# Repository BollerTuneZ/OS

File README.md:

# OS
BollerTuneZ Operating System

http://www.bollertunez.de/

git test

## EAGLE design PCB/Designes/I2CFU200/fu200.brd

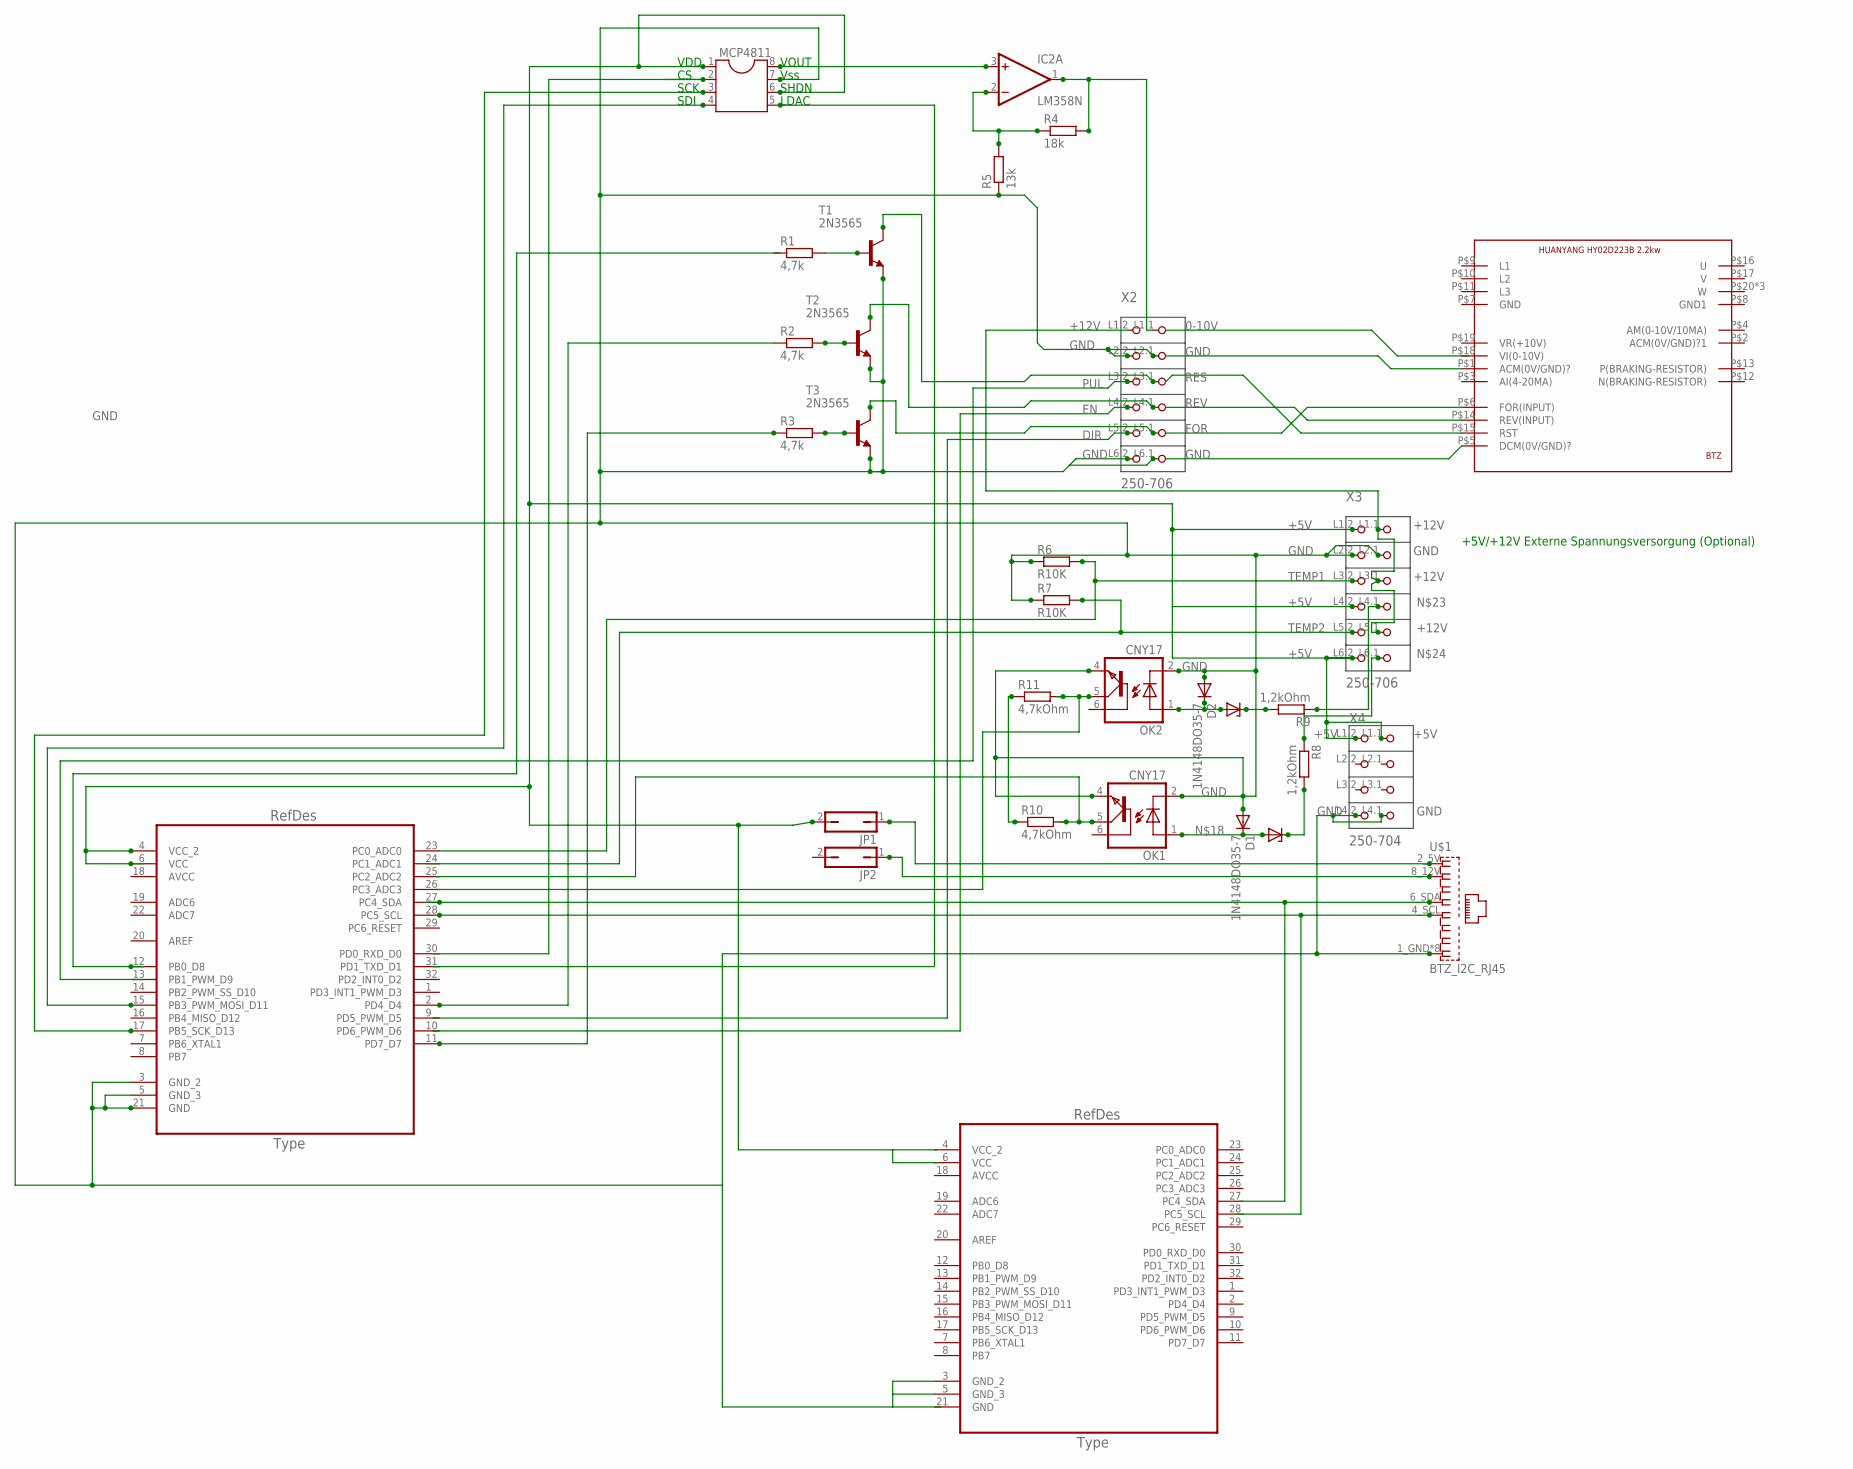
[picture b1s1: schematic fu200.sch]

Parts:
D1, D2: 1N4148DO35-7; DO35-7
IC2: LM358N; DIL08
JP1, JP2: JP1Q; JP1
MCP4811: DIL8; DIL08
OK1, OK2: CNY17; DIL06
R1, R2, R3: 4,7k; 0309/10
R4: 18k; 0204/7
R5: 13k; 0204/7
R6, R7: R10K; 0309/10
R8, R9: 1,2kOhm; 0204/7
R10, R11: 4,7kOhm; 0204/7
T1, T2, T3: 2N3565; TO92
U1, U2: ATMEGA328P-AU; QFP80P900X900X120-32N
U$1: BTZ_I2C_RJ45; RJ45
U$2: HUN_FU2
X2, X3: 250-706; P-250-706
X4: 250-704; P-250-704

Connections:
0-10V: IC2.1 (OUT), R4.2, X2.L1.1 (P1.1)
+5V: JP1.2, MCP4811.1, MCP4811.6, U1.4 (VCC_2), U1.6 (VCC), X3.L1.2 (P1.2), X3.L4.2 (P4.2), X3.L6.2 (P6.2), X4.L1.1 (P1.1), X4.L1.2 (P1.2)
+12V: X2.L1.2 (P1.2), X3.L1.1 (P1.1), X3.L3.1 (P3.1), X3.L5.1 (P5.1)
AVCC: U1.18 (AVCC), U2.18 (AVCC)
DIR: X2.L5.2 (P5.2)
EN: X2.L4.2 (P4.2)
FOR: T3.1 (C), X2.L5.1 (P5.1)
GND: D1.A, D2.A, MCP4811.7, OK1.2 (C), OK1.4 (EMI), OK2.2 (C), OK2.4 (EMI), R5.1, R6.1, R7.1, T1.3 (E), T2.3 (E), T3.3 (E), U1.3 (GND_2), U1.5 (GND_3), U1.21 (GND), U2.3 (GND_2), U2.5 (GND_3), U$1.1_GND (GND), U$1.3_GND (GND), U$1.5_GND (GND), U$1.7_GND (GND), U$1.G1 (GND), U$1.G2 (GND), U$1.G3 (GND), U$1.G4 (GND), X2.L2.1 (P2.1), X2.L2.2 (P2.2), X2.L6.1 (P6.1), X2.L6.2 (P6.2), X3.L2.1 (P2.1), X3.L2.2 (P2.2), X4.L4.1 (P4.1), X4.L4.2 (P4.2)
unnamed: R1.2, T1.2 (B)
unnamed: U1.27 (PC4_SDA), U$1.6_SDA (SDA)
unnamed: R3.2, T3.2 (B)
unnamed: U1.28 (PC5_SCL), U$1.4_SCL (SCL)
unnamed: JP2.1, U$1.8_12V (12V)
unnamed: JP1.1, U$1.2_5V (5V)
unnamed: R2.1, U1.2 (PD4_D4)
unnamed: R3.1, U1.11 (PD7_D7)
unnamed: R2.2, T2.2 (B)
unnamed: D1.C, OK1.1 (A)
unnamed: D2.C, OK2.1 (A)
unnamed: R10.1, R11.1
unnamed: OK2.5 (COL), R11.2
unnamed: R9.1, X3.L4.1 (P4.1)
unnamed: R8.1, X3.L6.1 (P6.1)
unnamed: OK1.5 (COL), R10.2
unnamed: IC2.3 (+IN), MCP4811.8
unnamed: MCP4811.3, U1.17 (PB5_SCK_D13)
unnamed: MCP4811.4, U1.15 (PB3_PWM_MOSI_D11)
unnamed: IC2.2 (-IN), R4.1, R5.2
PUL: X2.L3.2 (P3.2)
RES: T1.1 (C), X2.L3.1 (P3.1)
REV: T2.1 (C), X2.L4.1 (P4.1)
TEMP1: R6.2, U1.23 (PC0_ADC0), X3.L3.2 (P3.2)
TEMP2: R7.2, X3.L5.2 (P5.2)
V+: IC2.8 (V+)
V-: IC2.4 (V-)
VCC: U2.6 (VCC)
VCC_2: U2.4 (VCC_2)

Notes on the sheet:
VDD
SCK
SDI
VOUT
Vss
SHDN
LDAC
+5V/+12V Externe Spannungsversorgung (Optional)

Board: 2 copper layers, 29 parts (2 on the bottom side), 30 nets, no tracks yet.

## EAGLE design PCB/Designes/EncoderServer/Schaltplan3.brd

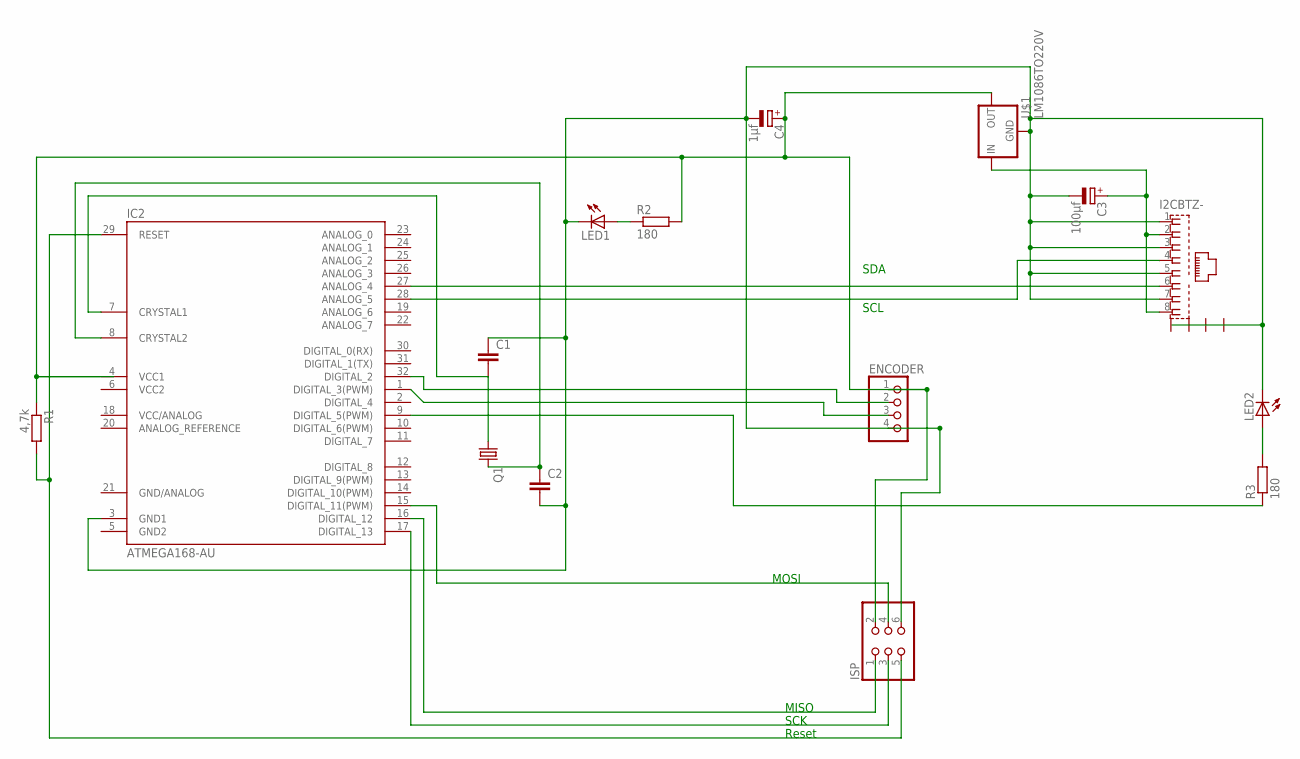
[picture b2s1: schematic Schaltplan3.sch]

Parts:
C1, C2: C-EU025-025X050; C025-025X050
C3: 100µf; E2,5-6
C4: 1µf; E2,5-6
ENCODER: PINHD-1X4; 1X04
I2CBTZ: RJ45
IC2: ATMEGA168-AU; TQFP32-08
ISP: PINHD-2X3; 2X03
LED1, LED2: LED5MM
Q1: CRYSTALHC49S; HC49/S
R1: 4,7k; 0204/7
R2, R3: 180; 0204/7
U$1: LM1086TO220V; TO220S

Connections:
GND2: IC2.5 (GND2)
GND/ANALOG: IC2.21 (GND/ANALOG)
unnamed: LED2.A, R3.2
unnamed: IC2.29 (RESET), ISP.5, R1.2
unnamed: C4.+, ENCODER.1, IC2.4 (VCC1), ISP.2, R1.1, R2.2, U$1.2 (OUT)
unnamed: C3.+, I2CBTZ.2, I2CBTZ.8, U$1.3 (IN)
unnamed: C1.2, IC2.7 (CRYSTAL1), Q1.1
unnamed: I2CBTZ.4, IC2.28 (ANALOG_5)
unnamed: I2CBTZ.6, IC2.27 (ANALOG_4)
unnamed: C2.1, IC2.8 (CRYSTAL2), Q1.2
unnamed: C1.1, C2.2, C3.-, C4.-, ENCODER.4, I2CBTZ.1, I2CBTZ.3, I2CBTZ.5, I2CBTZ.7, IC2.3 (GND1), ISP.6, LED1.K (C), LED2.K (C), U$1.1 (GND)
unnamed: ENCODER.3, IC2.1 (DIGITAL_3(PWM))
unnamed: ENCODER.2, IC2.32 (DIGITAL_2)
unnamed: IC2.17 (DIGITAL_13), ISP.3
unnamed: IC2.9 (DIGITAL_5(PWM)), R3.1
unnamed: LED1.A, R2.1
unnamed: IC2.16 (DIGITAL_12), ISP.1
unnamed: IC2.15 (DIGITAL_11(PWM)), ISP.4
VCC2: IC2.6 (VCC2)

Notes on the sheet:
MISO
SCK
MOSI
Reset
SDA
SCL

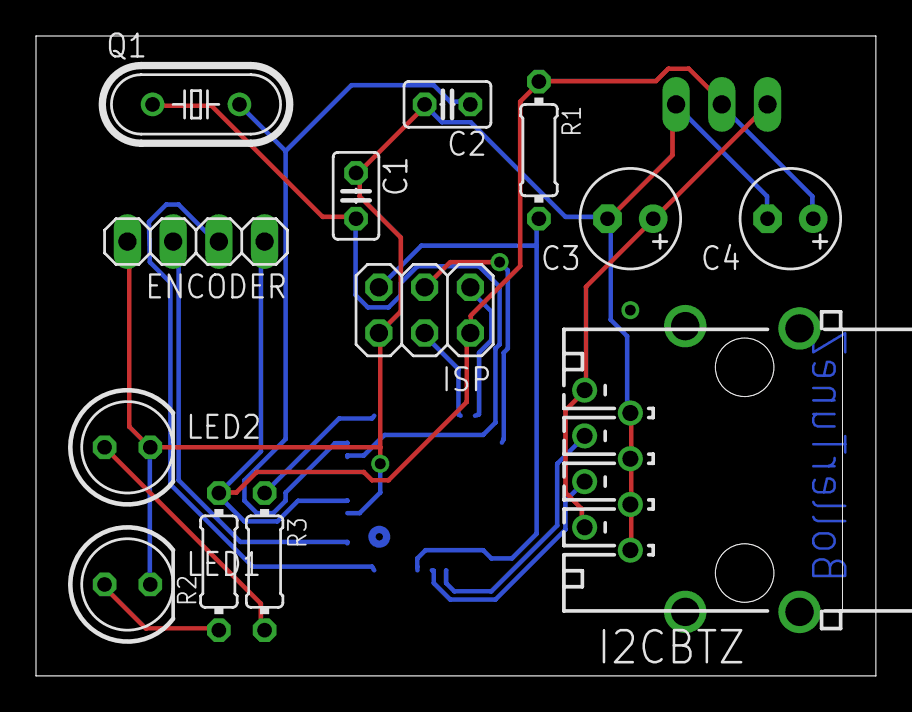
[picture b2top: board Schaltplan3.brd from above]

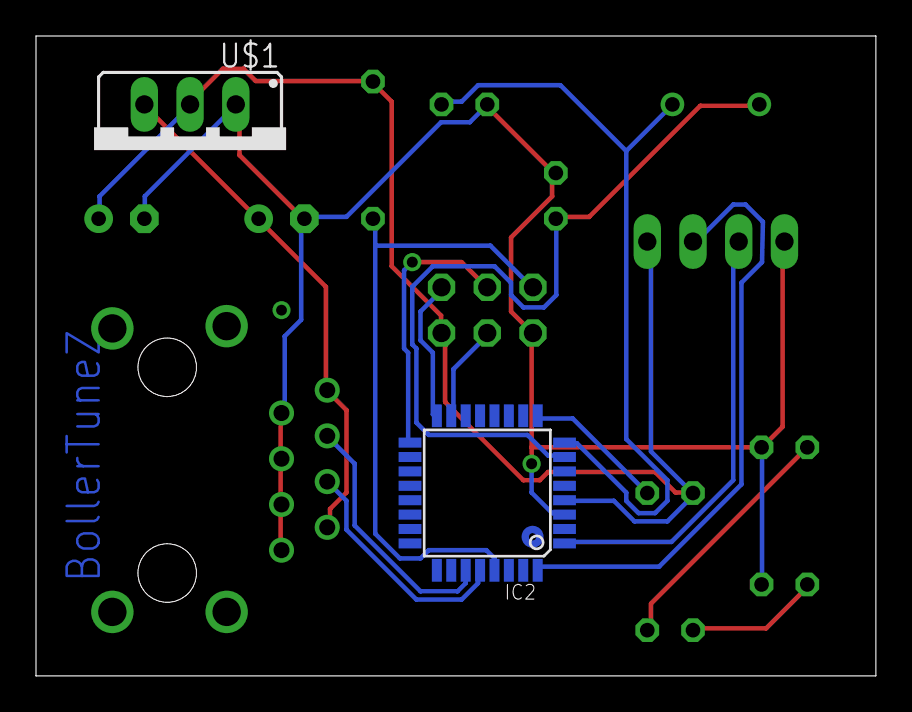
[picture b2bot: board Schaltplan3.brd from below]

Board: 2 copper layers, 46.7 x 35.6 mm, 15 parts (2 on the bottom side), 16 nets.

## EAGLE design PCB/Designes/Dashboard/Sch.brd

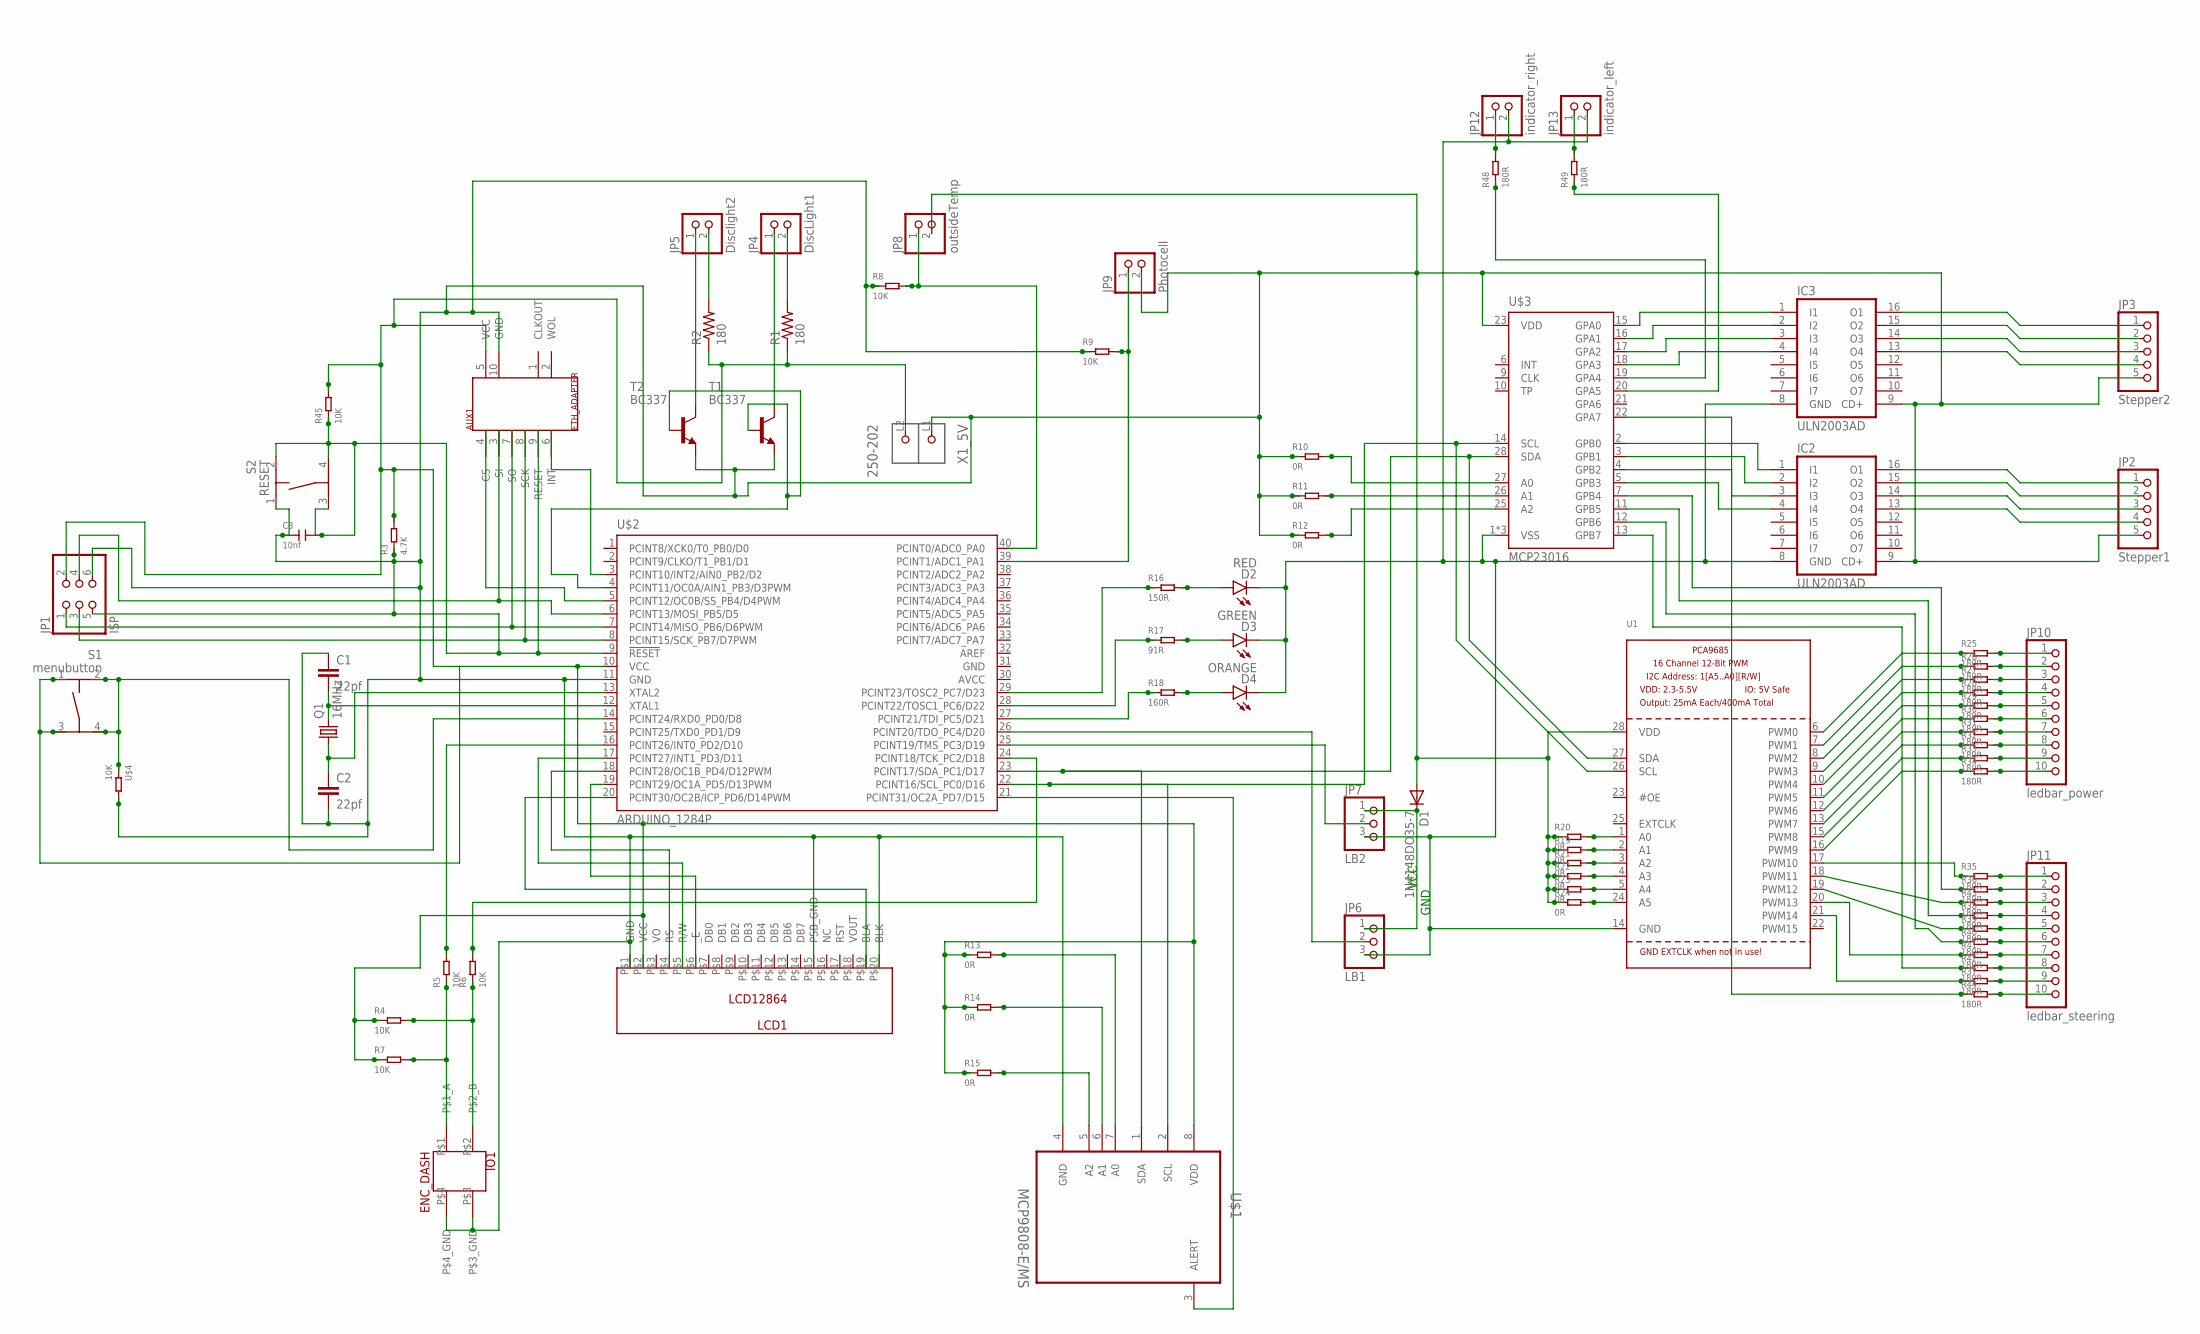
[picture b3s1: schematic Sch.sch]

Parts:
AUX1: ETH_ADAPTER; PINHEAD5X5
C1, C2: 22pf; C025-025X050
C3: 10nf; C0603
D1: 1N4148DO35-7; DO35-7
D2: RED; LED-0603
D3: GREEN; LED-0603
D4: ORANGE; LED-0603
IC2, IC3: ULN2003AD; SO16
IO1: ENC_DASH; PINHEAD2X2
JP1: ISP; 2X03
JP2: Stepper1; 1X05
JP3: Stepper2; 1X05
JP4: DiscLight1; 1X02
JP5: Disclight2; 1X02
JP6: LB1; 1X03
JP7: LB2; 1X03
JP8: outsideTemp; 1X02
JP9: Photocell; 1X02
JP10: ledbar_power; 1X10
JP11: ledbar_steering; 1X10
JP12: indicator_right; 1X02
JP13: indicator_left; 1X02
LCD1: LCD12864; PINHEAD1X20
Q1: 16MHz; HC49/S
R1, R2: 180; 0805-THM
R3: 4.7K; R0603
R4, R5, R6, R7, R8, R9, R45: 10K; R0603
R10, R11, R12, R13, R14, R15, R19, R20, R21, R22, R23, R24: 0R; R0603
R16: 150R; R0603
R17: 91R; R0603
R18: 160R; R0603
R25, R26, R27, R28, R29, R30, R31, R32, R33, R34, R35, R36, R37, R38, R39, R40, R41, R42, R43, R44, R48, R49: 180R; R0603
S1: menubutton; TASTER-9314_SMD
S2: RESET; TASTER-9314_SMD
T1, T2: BC337; TO92
U1: PCA9685; TSSOP28
U$1: MCP9808-E/MS; SOP65P490X110-8N
U$2: ARDUINO_1284P; DIL40
U$3: MCP23016; SO28W
U$4: 10K; R0805
X1_5V: 250-202; P-250-202

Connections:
AVCC: U$2.30 (AVCC)
DISCLIGHT1: T1.2 (B), T2.2 (B), U$2.4 (PCINT11/OC0A/AIN1_PB3/D3PWM)
GND: U$2.31 (GND)
unnamed: IC2.16 (O1), JP2.1
unnamed: IC2.15 (O2), JP2.2
unnamed: IC2.14 (O3), JP2.3
unnamed: IC2.13 (O4), JP2.4
unnamed: IC3.16 (O1), JP3.1
unnamed: IC3.15 (O2), JP3.2
unnamed: IC3.14 (O3), JP3.3
unnamed: IC3.13 (O4), JP3.4
unnamed: R36.1, U$3.7 (GPB4)
unnamed: JP5.1, T2.3 (C)
unnamed: JP5.2, R2.2
unnamed: JP4.2, R1.2
unnamed: JP4.1, T1.3 (C)
unnamed: S1.2, S1.4, U$2.14 (PCINT24/RXD0_PD0/D8), U$4.1
unnamed: IC3.1 (I1), U$3.15 (GPA0)
unnamed: C2.1, Q1.1, U$2.13 (XTAL2)
unnamed: IC3.2 (I2), U$3.16 (GPA1)
unnamed: C1.2, Q1.2, U$2.12 (XTAL1)
unnamed: IC3.3 (I3), U$3.17 (GPA2)
unnamed: D1.C, JP6.1, JP7.1
unnamed: R11.2, U$3.26 (A1)
unnamed: AUX1.7 (SO), JP1.1, U$2.7 (PCINT14/MISO_PB6/D6PWM)
unnamed: AUX1.8 (SCK), JP1.3, U$2.8 (PCINT15/SCK_PB7/D7PWM)
unnamed: IC3.4 (I4), U$3.18 (GPA3)
unnamed: AUX1.3 (SI), JP1.4, U$2.6 (PCINT13/MOSI_PB5/D5)
unnamed: R38.1, U$3.11 (GPB5)
unnamed: U$1.3 (ALERT), U$2.21 (PCINT31/OC2A_PD7/D15)
unnamed: IO1.P$2 (P$2_B), R4.2, R6.1
unnamed: AUX1.6 (INT), U$2.3 (PCINT10/INT2/AIN0_PB2/D2)
unnamed: AUX1.4 (CS), U$2.5 (PCINT12/OC0B/SS_PB4/D4PWM)
unnamed: U1.26 (SCL), U$1.2 (SCL), U$2.22 (PCINT16/SCL_PC0/D16), U$3.14 (SCL)
unnamed: U1.27 (SDA), U$1.1 (SDA), U$2.23 (PCINT17/SDA_PC1/D17), U$3.28 (SDA)
unnamed: IO1.P$1 (P$1_A), R5.1, R7.2
unnamed: IC2.1 (I1), U$3.2 (GPB0)
unnamed: IC2.2 (I2), U$3.3 (GPB1)
unnamed: LCD1.P$4 (RS), U$2.18 (PCINT28/OC1B_PD4/D12PWM)
unnamed: LCD1.P$5 (R/W), U$2.17 (PCINT27/INT1_PD3/D11)
unnamed: LCD1.P$6 (_E), U$2.19 (PCINT29/OC1A_PD5/D13PWM)
unnamed: LCD1.P$19 (BLA), U$2.20 (PCINT30/OC2B/ICP_PD6/D14PWM)
unnamed: R5.2, U$2.16 (PCINT26/INT0_PD2/D10)
unnamed: R6.2, U$2.24 (PCINT18/TCK_PC2/D18)
unnamed: IC2.3 (I3), U$3.4 (GPB2)
unnamed: IC2.4 (I4), U$3.5 (GPB3)
unnamed: R14.2, U$1.6 (A1)
unnamed: JP7.2, U$2.25 (PCINT19/TMS_PC3/D19)
unnamed: JP6.2, U$2.26 (PCINT20/TDO_PC4/D20)
unnamed: JP8.1, R8.2, U$2.40 (PCINT0/ADC0_PA0)
unnamed: R10.2, U$3.27 (A0)
unnamed: JP9.1, R9.2, U$2.39 (PCINT1/ADC1_PA1)
unnamed: R41.1, U1.20 (PWM13)
unnamed: R12.2, U$3.25 (A2)
unnamed: R13.2, U$1.7 (A0)
unnamed: R15.2, U$1.5 (A2)
unnamed: R39.1, U1.19 (PWM12)
unnamed: D2.A, R16.2
unnamed: D3.A, R17.2
unnamed: D4.A, R18.2
unnamed: R18.1, U$2.27 (PCINT21/TDI_PC5/D21)
unnamed: R17.1, U$2.28 (PCINT22/TOSC1_PC6/D22)
unnamed: R16.1, U$2.29 (PCINT23/TOSC2_PC7/D23)
unnamed: R24.2, U1.24 (A5)
unnamed: R23.2, U1.5 (A4)
unnamed: R22.2, U1.4 (A3)
unnamed: R21.2, U1.3 (A2)
unnamed: R19.2, U1.2 (A1)
unnamed: R20.2, U1.1 (A0)
unnamed: JP10.1, R25.2
unnamed: JP10.2, R26.2
unnamed: JP10.3, R27.2
unnamed: JP10.4, R28.2
unnamed: JP10.5, R29.2
unnamed: JP10.6, R30.2
unnamed: JP10.7, R31.2
unnamed: JP10.8, R32.2
unnamed: JP10.9, R33.2
unnamed: JP10.10, R34.2
unnamed: JP11.1, R35.2
unnamed: JP11.2, R36.2
unnamed: JP11.3, R43.2
unnamed: JP11.4, R38.2
unnamed: JP11.5, R39.2
unnamed: JP11.6, R40.2
unnamed: JP11.7, R41.2
unnamed: JP11.8, R42.2
unnamed: JP11.9, R37.2
unnamed: JP11.10, R44.2
unnamed: R25.1, U1.6 (PWM0)
unnamed: R26.1, U1.7 (PWM1)
unnamed: R27.1, U1.8 (PWM2)
unnamed: R28.1, U1.9 (PWM3)
unnamed: R29.1, U1.10 (PWM4)
unnamed: R30.1, U1.11 (PWM5)
unnamed: R31.1, U1.12 (PWM6)
unnamed: R32.1, U1.13 (PWM7)
unnamed: R33.1, U1.15 (PWM8)
unnamed: R34.1, U1.16 (PWM9)
unnamed: R35.1, U1.17 (PWM10)
unnamed: R43.1, U1.18 (PWM11)
unnamed: R37.1, U1.21 (PWM14)
unnamed: R40.1, U$3.12 (GPB6)
unnamed: AUX1.9 (RESET), C3.2, JP1.5, R45.1, S2.2, S2.3, S2.4, U$2.9 (!RESET)
unnamed: R42.1, U$3.13 (GPB7)
unnamed: R44.1, U$3.22 (GPA7)
unnamed: R48.1, U$3.19 (GPA4)
unnamed: R49.1, U$3.20 (GPA5)
unnamed: JP12.1, R48.2
unnamed: JP13.1, R49.2
unnamed: D2.C, D3.C, D4.C, IC2.8 (GND), IC3.8 (GND), JP6.3, JP7.3, JP12.2, JP13.2, U1.14 (GND), U$3.1 (VSS), U$3.8 (VSS), U$3.24 (VSS)
VCC: AUX1.5 (VCC)

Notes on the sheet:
VCC
GND

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
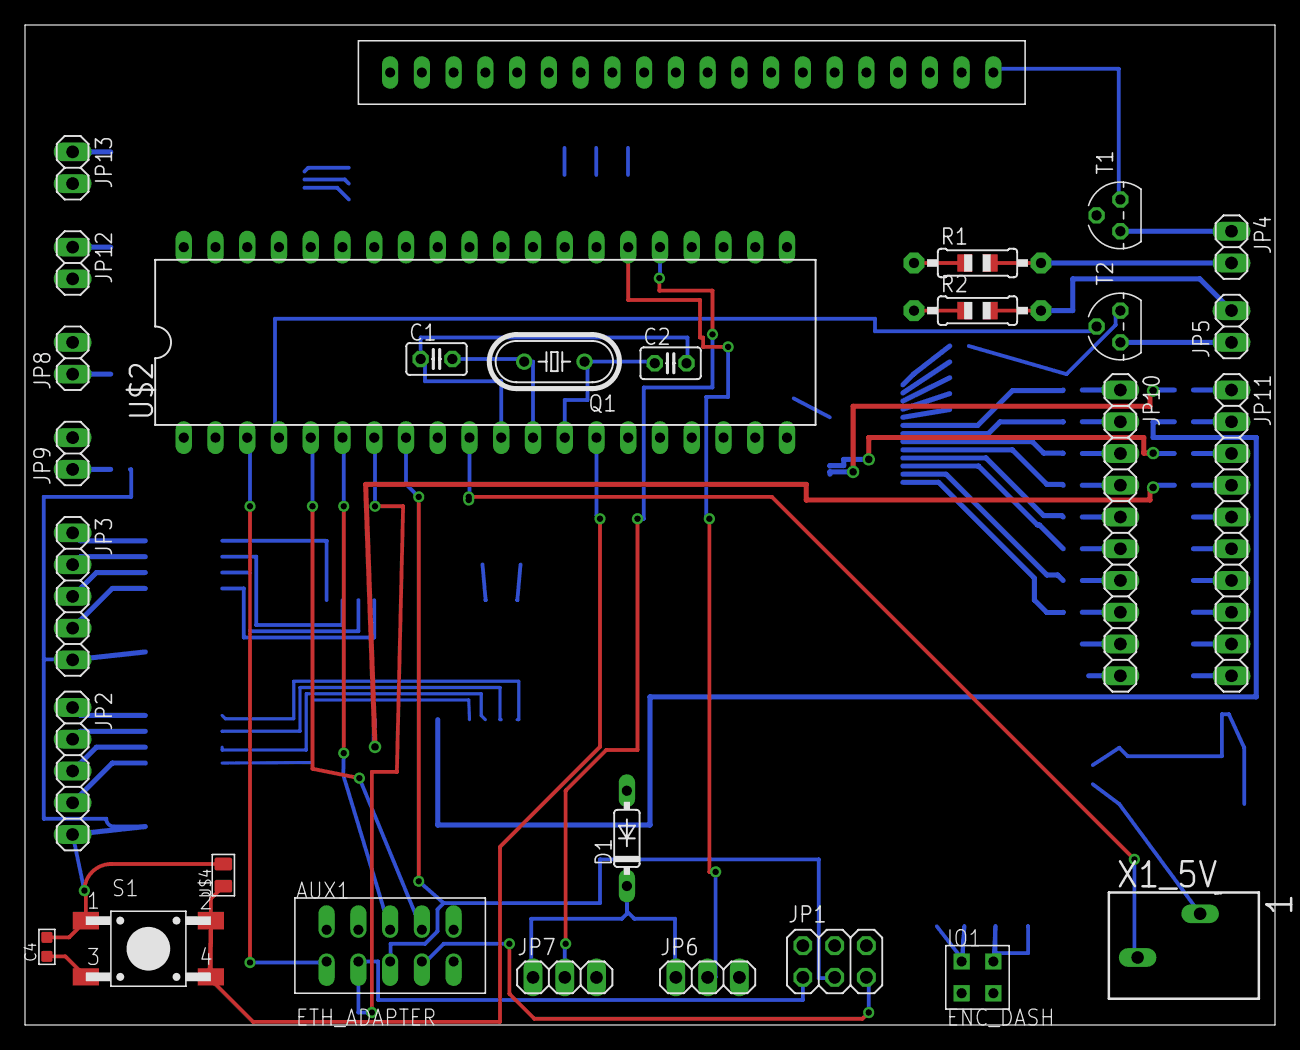
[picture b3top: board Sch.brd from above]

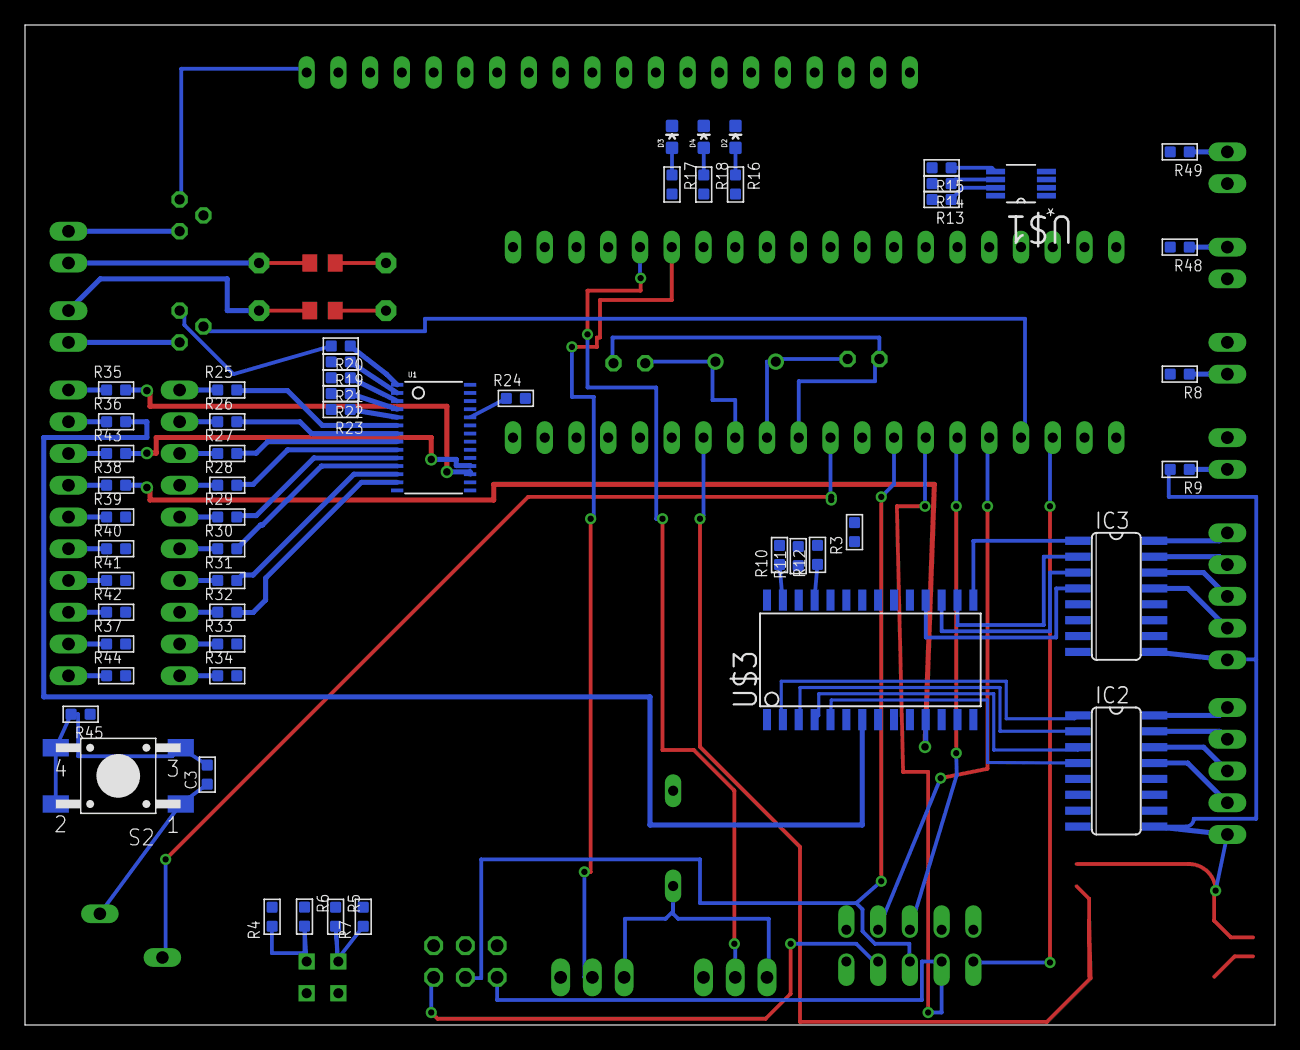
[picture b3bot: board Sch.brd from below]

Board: 2 copper layers, 100.0 x 80.0 mm, 84 parts (55 on the bottom side), 110 nets.

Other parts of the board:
C4: 10nf; C0603

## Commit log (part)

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2016-03-16 ready for testing gpio 4
2016-03-16 Licht Steuerung
    Licht kann nun über 3 Fader und 3 Buttons gesteuert werden. Die drei
    Buttons sind zum Links Rechts Blinken und wieder zurückzusetzen.
    und denn kann man noch mit den 3 Federn einmal Oder Licht Rücklicht und
    Beide zusammen Steuern.
2016-03-17 raspi
2016-03-22 layouts
2016-03-22 build able
2016-03-22 added logging of results
2016-03-22 testing with wiringPi
2016-03-22 not build able
2016-03-22 cmake
2016-03-23 buggy fucky
2016-03-23 changed class name of gpio driver
2016-03-23 syntax fix
2016-03-23 added pigpio test
2016-03-23 test
2016-03-23 test2
2016-03-25 blub
2016-04-03 clean
2016-04-03 better
2016-04-04 cmake changes
2016-04-04 bugfix
2016-04-04 set c++ standart to 11 for serv.app
2016-04-04 works
2016-04-04 build probs
2016-04-04 include adjustment
2016-04-04 build and run ok
2016-04-04 gpio driver init
2016-04-04 gpio test on raspi
2016-04-06 stepper driver
2016-04-21 pcbs
2016-04-24 dasd
2016-04-24 cmake lists
2016-04-24 fixes
2016-04-24 sytaxfix
2016-04-24 include fix
2016-04-25 thread fix
2016-04-26 test pthread
2016-04-26 simplified
2016-04-26 changes to std threads
2016-04-26 adss
2016-04-26 refactoring
2016-04-26 ready for testing
2016-04-26 enabled debug mode
2016-04-26 dbug
2016-04-26 more logging
2016-04-28 node core server
2016-04-29 Added node stepper driver
2016-04-29 package.json
2016-04-29 node js dependencies
2016-04-29 +git push
2016-04-29 logging
2016-04-29 init timer
2016-04-29 changed library
2016-04-30 node
2016-04-30 driver test added
2016-04-30 added softtest
2016-04-30 gitignore
2016-04-30 joystick test
2016-04-30 fuck
2016-04-30 delays
2016-04-30 fuck2
2016-05-01 testing with interval
2016-05-01 init funzt
2016-05-01 added loging
2016-05-01 asdasd
2016-05-01 writing implemented
2016-05-01 serial port
2016-05-01 added better int logic
2016-05-01 small changes
2016-05-01 save
2016-05-01 bugfixes
2016-05-01 modified test
2016-05-01 saver
2016-05-01 run able
2016-05-01 fixes and delay
2016-05-01 AUTOCOMMIT_UBUNTU
2016-05-01 AUTO_COMMIT_RPI
2016-05-02 working arduino sketch
2016-05-02 steering control written down
2016-05-03 goodnight
2016-05-04 steeringctrl changes with range and middle offset created steeringCtrlTest
2016-05-04 diffrent logic
2016-05-04 tada
2016-05-04 added power function to arduino
2016-05-04 arduino
2016-07-22 Clean. New start :)
2016-09-15 x
    x
2016-09-18 EncoderServer
    EncoderServer Schaltplan und Board überarbeitet.
2016-09-19 Schaltplan überarbeitet
    EncoderServer Schaltplan überarbeitet
    12V Versorgung über RJ45 oder 5V ?
    Noch ist ein LMxxxx drin.
2016-09-19 Schaltkasten
    Schaltkasten Schaltplan erstellt.
2016-09-24 Atmega328p eagle library
2016-09-24 Schaltkasten
2016-09-24 Added ATmega 328p
2016-09-24 lock file
2016-09-24 Library resistor led
2016-09-24 Umbau
2016-09-24 I2C Jack 8 fix
2016-10-04 I2CFU200 Schaltplan fertig
2016-10-04 Neues Board file
2016-10-08 .lck auf ignore
2016-10-08 Library ATmega 2560 16-au
2016-10-11 FU200
    Freuquenzumrichter als neues Device erstellt, Transistoren und wagt
    klemmen hinzugefügt
2017-01-08 Arduino Scripts

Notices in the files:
parts and their libraries:
SparkFun-LED: Licensing: Creative Commons ShareAlike 4.0 International - https://creativecommons.org/licenses/by-sa/4.0
